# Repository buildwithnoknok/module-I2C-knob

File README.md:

# noknok Knob

An I²C-controlled rotary encoder module for the noknok ecosystem.
Designed for smooth, reliable user input: volume control, menu navigation, parameter adjustment, and more.

---

## Overview

The **noknok Knob** uses a CH32V003J4M6 microcontroller to read a mechanical EC11 rotary encoder with integrated push button. It exposes position, delta, and button state over I²C using the standard noknok JST SH 4-pin connector. The I²C address is assigned dynamically at boot by the noknok Conductor — no address conflicts when using multiple modules.

Typical use cases:
- Volume / brightness control
- Menu navigation
- Parameter tuning (speed, mode, color)
- General UI input for kits and finished products

---

## Hardware

| Property | Value |
|---|---|
| PCB size | 20 × 20 mm |
| MCU | CH32V003J4M6 (SOP-8) |
| Encoder | EC11 rotary encoder with push button |
| Connector | JST SH 4-pin (Qwiic / STEMMA QT compatible) |
| Supply voltage | 3.3 V |
| Logic voltage | 3.3 V |
| Hardware version | v2.0 |

### Pinout (CH32V003J4M6 SOP-8)

| Pin name | Function |
|---|---|
| PA2 | Encoder A (active LOW, internal pull-up) |
| PD6 / PA1 | Encoder B (active LOW, read as PA1) |
| PC4 | Push button S2 (active LOW; S1 and C are grounded) |
| PC1 | I²C SDA |
| PC2 | I²C SCL |
| PD1 / PD4 / PD5 | SWDIO — firmware flashing (3-pad pogo pads, J3) + status LED (D2, active LOW) share the PD1/SWIO net |

### noknok Connector (JST SH 4-pin)

| Pin | Signal |
|---|---|
| 1 | GND |
| 2 | 3.3 V |
| 3 | SDA |
| 4 | SCL |

---

## Firmware

**Version: v2.3.0 (bootloader‑hosted)**

### Enumeration

The module uses the standard noknok dynamic enumeration protocol — no hardcoded I²C address.

**→ Full protocol spec:** [Ecosystem / software / enumeration.md](https://github.com/buildwithnoknok/Ecosystem/blob/main/software/enumeration.md)

### I²C Protocol (normal operation)

**Pico reads 4 bytes:**

| Byte | Content |
|---|---|
| 0–1 | Signed 16-bit position, big-endian |
| 2 | Signed 8-bit delta since last read (auto-clears on read) |
| 3 | Button state: `0x01` = pressed, `0x00` = released |

> Button state is suppressed for 150 ms after any rotation to prevent false triggers from mechanical shaft coupling.

**Pico writes:**

| Command | Effect |
|---|---|
| `[0x10]` | Reset position to 0 |
| `[0x11, posH, posL]` | Set position to signed 16-bit value |
| `[0xB0]` | Enter bootloader — reset into the I²C bootloader for an OTA firmware update (see [Firmware](#firmware-1)) |
| `[0xB1]` | Get version — standard noknok command; the next read returns 4 version bytes (see below) |

**Version read** — `GET_VERSION` (`0xB1`) is a **noknok ecosystem-standard** command (the `0xB0`–`0xBF` range is reserved for standard commands across every module). Write `0xB1`, then read **4 bytes**: `[PROTOCOL_VERSION, FW_MAJOR, FW_MINOR, FW_PATCH]` = `[0x01, 2, 3, 0]`. Lets the Conductor compare the installed version against the version required by the product manifest. **→ Full spec:** [Ecosystem / software / readme.md §5](https://github.com/buildwithnoknok/Ecosystem/blob/main/software/readme.md#5-standard-system-commands)

### Encoder counting

- Hardware EXTI interrupts on both edges of PA1 and PA2 catch every quadrature transition immediately.
- A sub-step accumulator divides by 2: **2 raw transitions = 1 position count**, giving exactly **1 count per physical detent**.

---

## Python Driver

Part of the [noknok Ecosystem](https://github.com/buildwithnoknok/Ecosystem) — see `software/pico/noknok.py`.

```python
from noknok import Conductor

c = Conductor()
c.enumerate()                  # discovers all modules (~3 s)

knob = c.knob[0]               # first knob by discovery order
# or: knob = c.role["volume"]  # by role name after setup_roles()

s = knob.read()
if s is not None:
    print(s.position)          # signed int, cumulative turns
    print(s.delta)             # change since last read (auto-clears)
    print(s.pressed)           # True if button held down

knob.reset()                   # set position to 0
knob.set_position(50)          # set to any signed 16-bit value
```

---

## Firmware

**v2.3.0 runs under the shared noknok I²C bootloader** ([module-I2C-bootloader](https://github.com/buildwithnoknok/module-I2C-bootloader)) — the module can be re‑flashed **over the I²C bus** (no SWDIO cable in the field). The application is linked at the `0x1400` offset (`app.ld`) above the 5 KB stage-0 + stage-1 bootloader (layout 2) and reserves the top 16 B of RAM for the bootloader handoff cell. Command `0xB0` drops the running module into the bootloader for an update.

```bash
cd firmware/src
make build   # compile the offset-linked application -> knob_firmware.bin
```

> ch32fun must be installed at `../ch32fun/` relative to `firmware/src/` — see [cnlohr/ch32v003fun](https://github.com/cnlohr/ch32v003fun) for setup.

Flashing: normally over I²C from the Pico (`module_flasher.py` in `brain-Pico`). A blank board needs the bootloader SWD‑flashed once first. SWD remains the unbrickable backstop — see *Recovery & SWD flashing* in the [bootloader README](https://github.com/buildwithnoknok/module-I2C-bootloader#recovery--swd-flashing). `make flash` here still does a one‑off SWD flash of the app for bench bring‑up.

---

## Changelog

### v2.3.0 — app base 0x1400 (bootloader layout 2)
Relinked at the `0x1400` flash offset (bootloader **layout 2**: 1 KB stage-0 + 4 KB stage-1 below the app; was `0x1000`). Firmware behaviour unchanged. **Not compatible with the legacy monolithic bootloader or a layout-1 stage-1** — such a module gets stage-0 + stage-1 v1.1.0 over SWD first, then this app over I²C. See [module-I2C-bootloader](https://github.com/buildwithnoknok/module-I2C-bootloader).

### v2.2.0 — watchdog + boot-health handshake (DEV-31)
Runs the independent watchdog (~2 s, kicked every main-loop pass) and writes `0` to `0x200007F8` the moment its I²C address is assigned — the app-health handshake with the stage-1 bootloader. Stage-1 counts watchdog resets and parks the module (error 7, rescued by the Conductor by UID) after three in a row, instead of booting a broken app forever. Contract: [Ecosystem / software / bootloader-update.md §3](https://github.com/buildwithnoknok/Ecosystem/blob/main/software/bootloader-update.md). No protocol or command change.

### v2.1 and earlier
See the git history.

## Status

| Item | Status |
|---|---|
| Hardware | v2.0 complete |
| Firmware | v2.3.0 complete (bootloader‑hosted, I²C OTA) |
| Python driver | Complete (`NoknokKnob` in [Ecosystem repo](https://github.com/buildwithnoknok/Ecosystem/tree/main/software/pico)) |
| Documentation | Complete |

---

## License

- Firmware / code: MIT — see [LICENSE](LICENSE).
- Hardware (schematics, PCB layout, fab files): CC BY-SA 4.0 — see [LICENSE-hardware](LICENSE-hardware).

## Trademarks

**noknok** is a registered trademark in Switzerland (Swissreg 1300007033).

Qwiic is a registered trademark of SparkFun Electronics, Inc. STEMMA QT is a
trademark of Adafruit Industries, LLC. Both are named here only to state
connector compatibility - noknok is not affiliated with, endorsed by, or
sponsored by either company.
---

---

## Safety & Liability

noknok hardware is an electronic device and a DIY/maker kit. You assemble, modify, flash, power, and operate it at your own risk, and it is provided as is, without warranty. See the full notice: [License, Safety & Liability](https://buildwithnoknok.github.io/safety-and-license/).

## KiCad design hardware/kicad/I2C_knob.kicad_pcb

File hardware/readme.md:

# Hardware — noknok Knob

Hardware design files for the noknok Knob module (CH32V003J4M6 — I2C rotary encoder with integrated push button).

- KiCad project: `kicad/I2C_knob.*`
- Schematic (PDF): `module-I2C-knob-Schematics.pdf`
- BOM: `module_I2C-knob-BOM.xls`
- Board renders: `module-I2C-rotaryencoder-front.png`, `module-I2C-rotaryencoder-back.png` *(pre-V2 renders — pending re-export)*

Hardware is licensed CC BY-SA 4.0 (see `../LICENSE-hardware`). Connector, flashing and mounting standards follow the [noknok Ecosystem guidelines](https://github.com/buildwithnoknok/Ecosystem) (electrical + mechanical).

---

## Hardware Change Record

### v2.0 — changes from v1.0
- **Status indicator LED on PD1** (in parallel with the SWIO flashing line — zero extra GPIO). Active-low: `+3V3_PROT → R2 (2.2 kΩ) → D2 anode; D2 cathode → PD1/SWIO`. Driven by the bootloader (off = app running, slow pulse = updating/recovering, solid = error). Parts: red 0603 LED (LCSC C2286) + 2.2 kΩ 0603 (LCSC C4190).
- **Removed both castellated edge pads** — the 5-pin flashing edge and the redundant I2C edge (unreliable to contact). I2C is via the JST-SH (Qwiic) connectors J1/J2 only.
- **New flashing interface (J3)** — noknok flash pads (`noknok_FlashPads_I2C-module_1x3_M2.5`): 3 single-side SMD pogo pads (GND / SWIO / VCC) plus an embedded M2.5 keyed mounting hole, from the noknok KiCad library in the Ecosystem repo. Pad row is offset toward the keyed hole (not centered) so a 180°-flipped clamp contact can't seat and reverse-power the board.
- **Second mounting hole (H1)** — plain `noknok_MountingHole_2.5mm_M2.5`, diagonally opposite the flash-pad hole, center (2.25, 2.25) mm from the board corner.
- **Removed the on-board I²C pull-up resistors** (previously R2/R3) — pull-ups now live on the host (Conductor), not per module (avoids stacking on the shared bus). The host must provide the bus pull-ups (proposed 3.3 kΩ); a noknok pull-up PCB covers third-party hosts that lack them. See the [I²C Pull-up Resistor Strategy ADR](https://noknokdev.atlassian.net/wiki/spaces/SD/pages/82280449). *(Note: `R2` is reused below for the new status-LED resistor — it is not the old pull-up.)*
- **R1 (VDD series) stays 10 Ω** — the knob has no spiky load on VDD (unlike the buzzer's beep-current 10Ω→1Ω fix), so the standard default is unchanged.

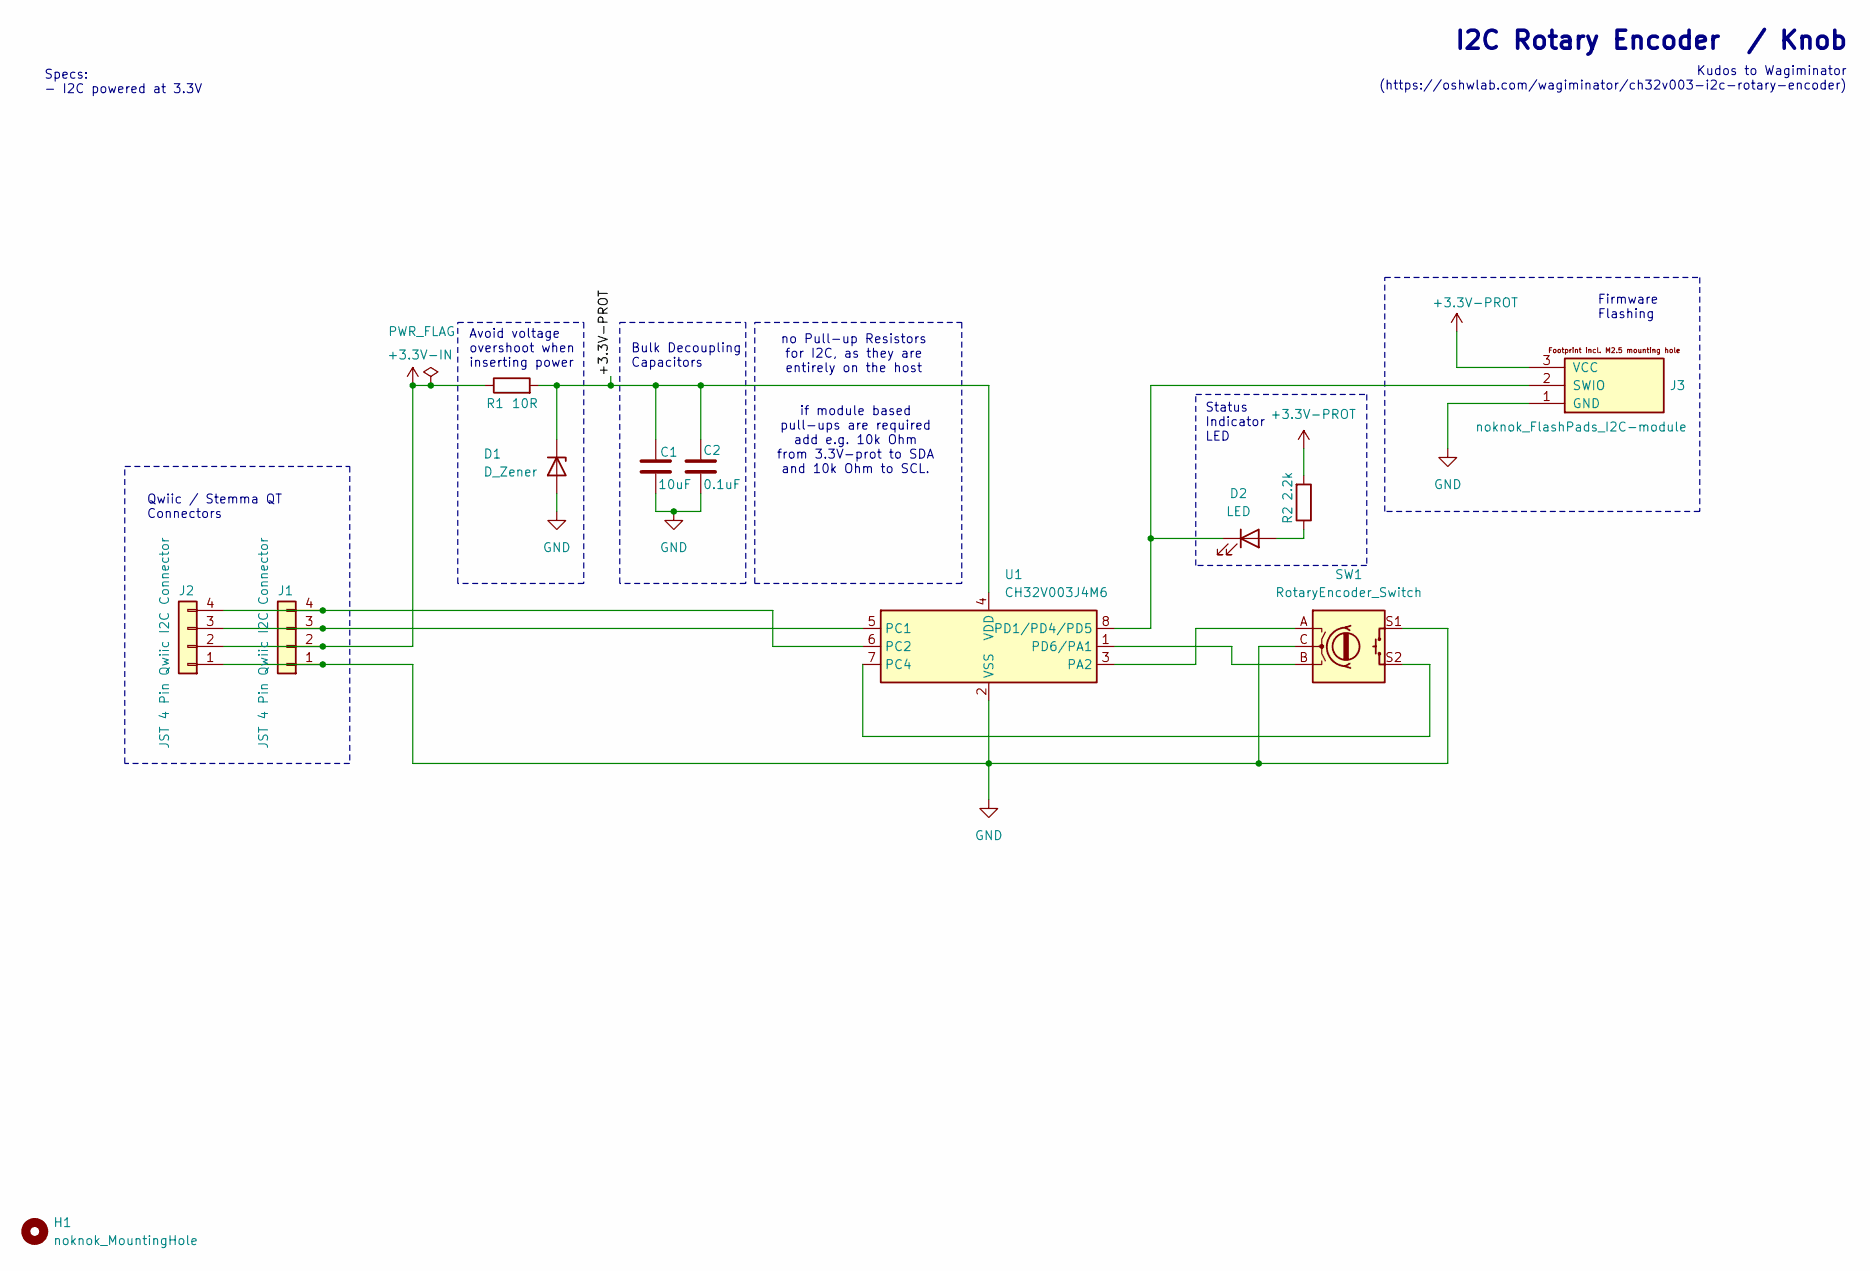
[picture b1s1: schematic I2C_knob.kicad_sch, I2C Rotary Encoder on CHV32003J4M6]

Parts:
C1: 10uF; C_0603_1608Metric_Pad1.08x0.95mm_HandSolder
C2: 0.1uF; C_0603_1608Metric_Pad1.08x0.95mm_HandSolder
D1: D_Zener; D_SOD-323
D2: LED; LED_0603_1608Metric
H1: noknok_MountingHole; noknok_MountingHole_2.5mm_M2.5
J1, J2: JST 4 Pin Qwiic I2C Connector; JST_SH_SM04B-SRSS-TB_1x04-1MP_P1.00mm_Horizontal
J3: noknok_FlashPads_I2C-module; noknok_FlashPads_I2C-module_1x3_M2.5
R1: 10R; R_0603_1608Metric
R2: 2.2k; R_0603_1608Metric
SW1: RotaryEncoder_Switch; RotaryEncoder_Alps_EC11E-Switch_Vertical_H20mm
U1: CH32V003J4M6; JEITA_SOIC-8_3.9x4.9mm_P1.27mm

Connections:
+3.3V-IN: J1.2, J2.2, R1.1
+3.3V-PROT: C1.1, C2.1, D1.1 (K), J3.3 (VCC), R1.2, R2.2, U1.4 (VDD)
GND: C1.2, C2.2, D1.2 (A), J1.1, J2.1, J3.1 (GND), SW1.C, SW1.S1, U1.2 (VSS)
unnamed: D2.2 (A), R2.1
unnamed: D2.1 (K), J3.2 (SWIO), U1.8 (PD1/PD4/PD5)
unnamed: J1.3, J2.3, U1.5 (PC1)
unnamed: J1.4, J2.4, U1.6 (PC2)
unnamed: SW1.A, U1.3 (PA2)
unnamed: SW1.S2, U1.7 (PC4)
unnamed: SW1.B, U1.1 (PD6/PA1)

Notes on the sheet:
Avoid voltage overshoot when inserting power
Specs: - I2C powered at 3.3V
I2C Rotary Encoder / Knob
if module based pull-ups are required add e.g. 10k Ohm from 3.3V-prot to SDA and 10k Ohm to SCL.
Status Indicator LED
no Pull-up Resistors for I2C, as they are entirely on the host
Firmware Flashing
Qwiic / Stemma QT Connectors
Kudos to Wagiminator (https://oshwlab.com/wagiminator/ch32v003-i2c-rotary-encoder)
Bulk Decoupling Capacitors

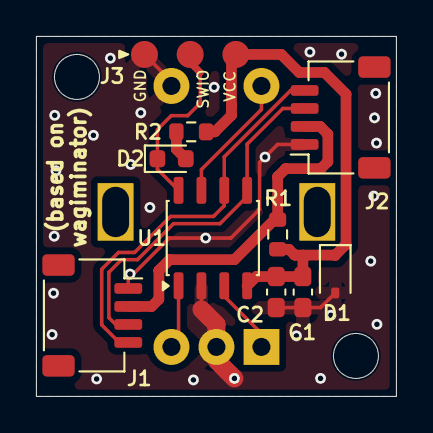
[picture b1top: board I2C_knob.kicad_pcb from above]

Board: 2 copper layers, 20.0 x 20.0 mm, 12 parts (1 on the bottom side), 10 nets.

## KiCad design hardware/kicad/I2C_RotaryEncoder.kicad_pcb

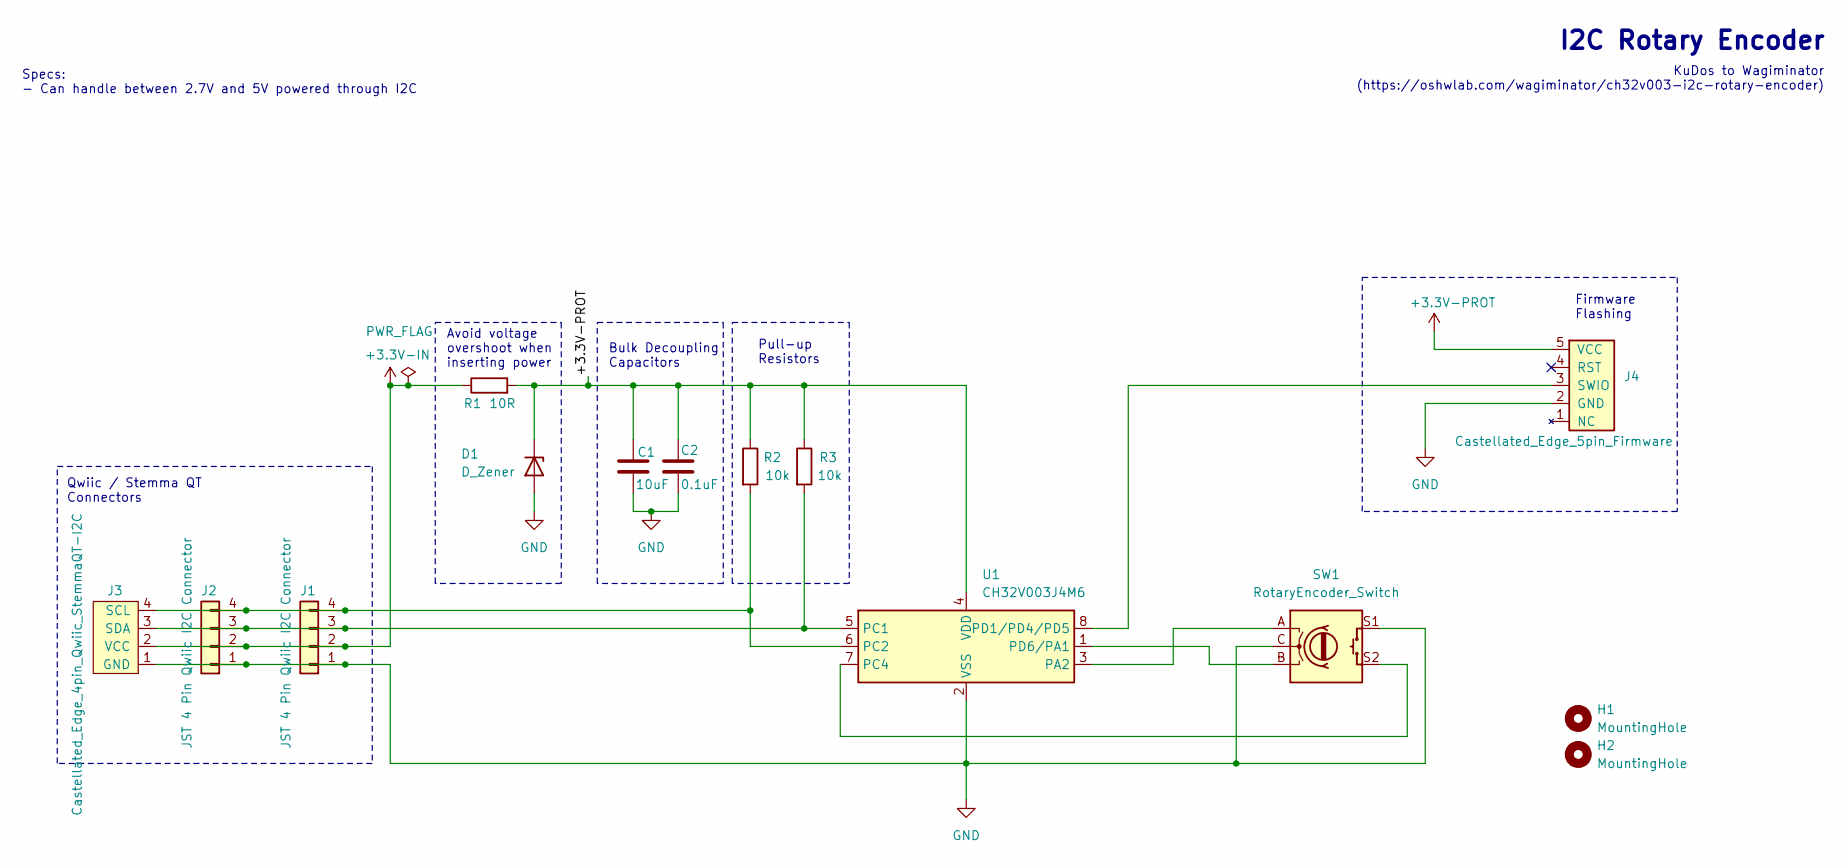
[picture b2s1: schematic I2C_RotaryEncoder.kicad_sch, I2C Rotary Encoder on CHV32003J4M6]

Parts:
C1: 10uF; C_0603_1608Metric_Pad1.08x0.95mm_HandSolder
C2: 0.1uF; C_0603_1608Metric_Pad1.08x0.95mm_HandSolder
D1: D_Zener; D_SOD-323
H1, H2: MountingHole; MountingHole_2.2mm_M2
J1, J2: JST 4 Pin Qwiic I2C Connector; JST_SH_SM04B-SRSS-TB_1x04-1MP_P1.00mm_Horizontal
J3: Castellated_Edge_4pin_Qwiic_StemmaQT-I2C; Castellated_edge_pad_I2C_4pin
J4: Castellated_Edge_5pin_Firmware; Castellated_edge_pad_Firmware
R1: 10R; R_0603_1608Metric
R2, R3: 10k; R_0603_1608Metric_Pad0.98x0.95mm_HandSolder
SW1: RotaryEncoder_Switch; RotaryEncoder_Alps_EC11E-Switch_Vertical_H20mm
U1: CH32V003J4M6; JEITA_SOIC-8_3.9x4.9mm_P1.27mm

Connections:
+3.3V-IN: J1.2, J2.2, J3.2 (VCC), R1.1
+3.3V-PROT: C1.1, C2.1, D1.1 (K), J4.5 (VCC), R1.2, R2.1, R3.1, U1.4 (VDD)
GND: C1.2, C2.2, D1.2 (A), J1.1, J2.1, J3.1 (GND), J4.2 (GND), SW1.C, SW1.S1, U1.2 (VSS)
unnamed: J1.3, J2.3, J3.3 (SDA), R3.2, U1.5 (PC1)
unnamed: J1.4, J2.4, J3.4 (SCL), R2.2, U1.6 (PC2)
unnamed: J4.3 (SWIO), U1.8 (PD1/PD4/PD5)
unnamed: SW1.A, U1.3 (PA2)
unnamed: SW1.S2, U1.7 (PC4)
unnamed: SW1.B, U1.1 (PD6/PA1)

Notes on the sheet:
Avoid voltage overshoot when inserting power
Specs: - Can handle between 2.7V and 5V powered through I2C
I2C Rotary Encoder
Firmware Flashing
Qwiic / Stemma QT Connectors
KuDos to Wagiminator (https://oshwlab.com/wagiminator/ch32v003-i2c-rotary-encoder)
Bulk Decoupling Capacitors
Pull-up Resistors

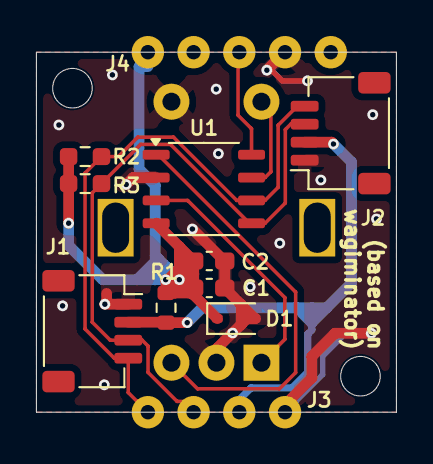
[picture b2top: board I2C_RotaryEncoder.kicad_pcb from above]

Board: 2 copper layers, 20.0 x 20.0 mm, 14 parts (1 on the bottom side), 9 nets.

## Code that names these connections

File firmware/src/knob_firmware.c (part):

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 * CH32V003J4M6 (SOP-8)  |  Stack: cnlohr/ch32fun
 *
 * ── Hardware ─────────────────────────────────────────────────────────────
 *   PA2          Encoder A (active LOW, internal pull-up)
 *   PD6/PA1      Encoder B (active LOW, internal pull-up; read as PA1 via GPIOA)
 *   PC4          Encoder push button S2 (active LOW; S1 and C are grounded)
 *   PC1          I2C SDA
 *   PC2          I2C SCL
 *
 * ── Encoder counting ─────────────────────────────────────────────────────
 *   EXTI interrupts on both edges of PA1 and PA2 (EXTI1 + EXTI2, port A).
 *   Gray-code lookup table → ±1 per quadrature transition.
 *   A standard EC11 with 4 pulses/detent gives 4 counts per click.
 *
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{
    RCC->APB2PCENR |= RCC_APB2Periph_GPIOA | RCC_APB2Periph_GPIOC;

    /* PA1 (ENC_B) and PA2 (ENC_A): input with pull-up */
    GPIOA->CFGLR &= ~((0xF << (1 * 4)) | (0xF << (2 * 4)));
    GPIOA->CFGLR |=  ((0x8 << (1 * 4)) | (0x8 << (2 * 4)));
    GPIOA->BSHR   =  (1 << 1) | (1 << 2);

    /* PC4: input with pull-up (button S2, active LOW; S1+C are grounded) */
    GPIOC->CFGLR &= ~(0xF << (4 * 4));
    GPIOC->CFGLR |=  (0x8 << (4 * 4));
    GPIOC->BSHR   =  (1 << 4);
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
static inline uint8_t read_enc_ab(void)
{
    /* A = PA2 (active low), B = PA1 (active low) — per Wagiminator reference.
     * Invert both so 1 means "encoder contact closed". */
    uint8_t a = !((GPIOA->INDR >> 2) & 1);   /* PA2 = ENC_A */
    uint8_t b = !((GPIOA->INDR >> 1) & 1);   /* PA1 = ENC_B */
    return (a << 1) | b;
}

static inline uint8_t read_btn_raw(void)
{
    return ((GPIOC->INDR >> 4) & 1) ? 0 : 1;   /* PC4, active LOW */
}


/* ═══════════════════════════════════════════════════════════════════════════
 * EXTI  —  hardware interrupts on both edges of PA1 (EXTI1) and PA2 (EXTI2)
 *   Catches every quadrature transition immediately, regardless of main loop
 *   speed. Both EXTI1 and EXTI2 share EXTI7_0_IRQn on CH32V003.
 * ═══════════════════════════════════════════════════════════════════════════ */
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
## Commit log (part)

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2026-05-08 Create hardware folder
2026-05-08 Create hardware/kicad folder
2026-05-08 Add Kicad project files
2026-05-08 Add schematics
2026-05-08 Upload PCB images
2026-05-08 Create firmware folder
2026-05-08 Create firmware/src folder
2026-05-08 Create firmware/bin folder
2026-05-08 Create docs folder
2026-06-01 Update product name to # noknok Knob
2026-06-01 Add knob firmware v1.0 - dynamic I2C enumeration, quadrature encoder, button
2026-06-01 Add Makefile for knob firmware
2026-06-01 Add funconfig.h for knob firmware
2026-06-01 Fix phantom button presses: rotation lockout 150ms + debounce 50ms
2026-06-01 v1.2: EXTI interrupts for encoder; button forced-0 during rotation lockout
2026-06-01 v1.3: fix encoder A/B swap and active-low polarity (per Wagiminator reference)
2026-06-01 v1.4: fix button pin - PC4 not PD6; remove erroneous GPIOD init
2026-06-01 v1.5: sub-step accumulator for 1 count per detent
2026-06-01 Update README: complete pinout, firmware v1.5 protocol, Python driver docs
2026-06-01 Fix README formatting: restore code fences and 0x literals
2026-06-01 fix: clear enc_delta atomically in ISR to prevent race condition on fast rotation
2026-06-01 docs: remove enumeration detail, link to Ecosystem/software/enumeration.md
2026-06-09 Add released firmware binary to firmware/bin
    Track the distributable offset-linked app image (flashed over I2C by the
    Pico). Adds a .gitignore exception so firmware/bin/*.bin is versioned while
    build artifacts elsewhere stay ignored.
2026-06-10 firmware v2.1: add GET_VERSION (0xB1) standard command (DEV-1)
2026-06-10 Update released firmware binary for GET_VERSION (DEV-1)
2026-06-11 Add MIT + CC BY-SA 4.0 licenses and License/Safety README sections for public release
2026-06-23 chore: remove redundant firmware/.keep (folder now has content)
2026-06-23 chore: remove redundant firmware/bin/.keep (folder now has content)
2026-06-23 chore: remove redundant firmware/src/.keep (folder now has content)
2026-06-23 chore: remove redundant hardware/.keep (folder now has content)
2026-06-23 chore: remove redundant hardware/kicad/.keep (folder now has content)
